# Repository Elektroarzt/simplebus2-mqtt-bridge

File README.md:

# Simplebus2 MQTT Bridge 

### Table of contents
[1. Overview](#Overview)  
[2. Software](#Software)  
[3. Hardware](#Hardware)  
[4. Mechanics](#Mechanics)  
[5. Disclaimer](#Disclaimer)  
[6. Credits](#Credits) 

## Overview

This project focuses on integrating Comelit intercom systems running the Simplebus2 protocol into a Smart Home, typically equipped with an MQTT broker for information exchange. The following functions have been implemented:

-   Doorbell signal main entrance
-   Doorbell signal apartment door
-   Opening main entrance door
-   Ring-to-Open (automatic opening)
-   Permanent web configuration UI (dark theme)
-   Home Assistant MQTT auto-discovery
-   Configurable MQTT topic prefix (default `SimpleBus`)
-   WiFi provisioning portal (first boot / factory reset)
-   Teach-in of intercom address
-   OTA updates (URL or file upload)

**Current firmware: 2.0.0** — see [software/docs/RELEASE-NOTES.md](software/docs/RELEASE-NOTES.md) and the [setup guide](software/docs/SETUP-GUIDE.md).

## Software

### Build and flash (PlatformIO)

```bash
cd software
pio run                 # build
pio run -t upload       # flash via USB
```

Target: ESP32-C3 (`esp32-c3-devkitm-1` / Seeed XIAO ESP32C3).

Pre-built binaries for **v2.0.0**:

| File | Use |
|------|-----|
| [`software/firmware/simplebus2-firmware-2.0.0.bin`](software/firmware/simplebus2-firmware-2.0.0.bin) | OTA / app update (same settings version only — see upgrade note) |
| [`software/firmware/simplebus2-merged-2.0.0.bin`](software/firmware/simplebus2-merged-2.0.0.bin) | Full flash from `0x0` (after erase) |

### First boot — WiFi

On first boot (or after factory reset) the bridge opens AP **`Simplebus2-Bridge`** (open network). Connect and open `http://192.168.4.1/` to set home WiFi. After joining the LAN, open:

- `http://Simplebus2-Bridge.local/` or the device IP

### Permanent web interface

Status, WiFi, MQTT (broker, credentials, **topic prefix**), device parameters (address, gain, threshold, Ring-to-Open duration), OTA, restart / factory reset:

ESP32 WiFi is **2.4 GHz only**. Prefer Chrome or Edge for OTA upload.

### Hardware tuning

**Gain** and **threshold (mV)** adapt to cable length and bus loading. Gain ≈ OPV amplification; threshold = comparator level before the signal reaches the ESP32. **Gain 20 / threshold 600 mV** works well for ~20 m cable in tested installations. See also [software/docs/tuning-process.md](software/docs/tuning-process.md).

### Ring-to-Open

Enable via MQTT (`<prefix>/RingToOpen`) or Home Assistant switch. Duration is set in the web UI or via `<prefix>/SetRingToOpenTime` (1–1440 minutes). **Ring-to-Open only opens on Entry Door rings**, not Floor Door. After a successful auto-open, RtO turns off.

### Firmware update (OTA)

In the web UI: paste an HTTP URL to a `.bin` and **OTA Flash**, or upload `simplebus2-firmware-2.0.0.bin` via **Upload & Flash**. Within the same settings layout version, EEPROM is kept — see **Upgrading from older firmware** below.

### Address adjustment

Each intercom unit has an 8-bit address (DIP switch S1, LSB). Example table:

 Switch No.| 1 | 2 | 3 | 4 |  5 |  6 |  7 |  8  |
 --------- |:-:|:-:|:-:|:-:|:--:|:--:|:--:|:---:|
 Value     | 1 | 2 | 4 | 8 | 16 | 32 | 64 | 128 |

Teach-in: hold SW1 3–4 s (LED double-blink), then ring within 3 minutes — or use MQTT `StartTeachIn` / set address in the web UI.

### MQTT data structure

Default topic prefix: **`SimpleBus`** (configurable). Change in the web UI if you prefer another root.

**Published topics**

 Topic                          | Values         | Notes
 ------------------------------ |:--------------:| ---------------------------------------------------
 `<prefix>/FloorDoor`           | ON             | bell rings on floor door of apartment
 `<prefix>/EntryDoor`           | ON             | bell rings on entry door of building
 `<prefix>/RingToOpenStatus`    | ON / OFF       | Ring-to-Open active or off (retained)
 `<prefix>/RingToOpenOpened`    | ON             | door opened via Ring-to-Open
 `<prefix>/RingToOpenTime`      | minutes        | current RtO duration (retained)
 `<prefix>/Heartbeat`           | ON             | every 5 min
 `<prefix>/availability`        | online         | published on connect

**Subscribed topics**

 Topic                          | Values         | Notes
 ------------------------------ |:--------------:| ---------------------------------------------------
 `<prefix>/OpenDoor`            | ON             | open the door
 `<prefix>/RingToOpen`          | ON / OFF / min | enable RtO (optional duration)
 `<prefix>/SetRingToOpenTime`   | 1 … 1440       | set RtO duration in minutes
 `<prefix>/SetGain`             | 2 … 40         | amplifier gain (default 20)
 `<prefix>/SetComparatorVoltage`| 100 … 1500     | threshold mV (default 600)
 `<prefix>/StartConfigMode`     | ON             | start WiFi AP portal
 `<prefix>/StartTeachIn`        | ON / OFF       | teach-in / cancel
 `<prefix>/Restart`             | ON             | restart ESP32

### Home Assistant

On MQTT connect the bridge publishes MQTT discovery. Entities appear under device **Simplebus2 Bridge** (Entry/Floor doorbell, Open Door button, Ring-to-Open switch & duration, etc.). Details: [software/docs/SETUP-GUIDE.md](software/docs/SETUP-GUIDE.md).

### Highlights vs previous public firmware

- **Robust Simplebus2 bus decoder** — state machine + ISR ring buffer, tighter timing, longer duplicate window (fixes double publish / false positives); see [RELEASE-NOTES](software/docs/RELEASE-NOTES.md)
- Permanent web UI, configurable MQTT prefix (**default still `SimpleBus`**), HA MQTT discovery, safer ESP32-C3 restart (`safeRestart` / GPIO9)

### Upgrading from older firmware (previous public sketch)

**Device settings in EEPROM are not migrated.** The old firmware stored MQTT/broker/gain/address without a settings-version header; this release uses a new `Settings` layout (`SETTINGS_VERSION = 3`). On first boot after the upgrade the bridge detects a version mismatch, **wipes those EEPROM fields, and loads factory defaults**.

| Data | Survives upgrade? |
|------|-------------------|
| WiFi SSID / password (WiFiManager NVS) | Usually **yes** |
| MQTT broker, user, password | **No — re-enter** |
| Topic prefix | **No — defaults to `SimpleBus`** |
| Intercom address, gain, threshold | **No — re-enter** |
| Ring-to-Open duration / automation flag | **No — re-enter** |

After flashing, open the web UI (`http://Simplebus2-Bridge.local/` or the device IP) and re-enter MQTT + device parameters. Have your previous values ready before you update.

### Breaking changes (previous public firmware → 2.0.0)

- **EEPROM layout incompatible** — MQTT and device settings must be re-entered (see above)
- WiFi AP name **`Config_MQTT_SimpleBus_2` / `Config_MQTT_SimpleBus2` → `Simplebus2-Bridge`**
- Configuration primarily via **permanent web UI** (not only WiFiManager menus)

### Dependencies (PlatformIO)

| Component | Version | Notes |
| --------- | ------- | ----- |
| PubSubClient | ^2.8 | `lib_deps` |
| WiFiManager | ^2.0.17 | `lib_deps` |
| Debounce | local | `software/lib/Debounce` |
| EEPROM, WiFi, Wire, WebServer, HTTPUpdate | Arduino-ESP32 | framework |

### Issue fixes in 2.0.0

- Correct comparison in `writeMessageToIntercom` (`msgCode == MSG_OPEN_DOOR`) — fixes [#13](https://github.com/Elektroarzt/simplebus2-mqtt-bridge/issues/13)
- `structInitialized()` uses `strlen` / settings version instead of `sizeof` on char arrays — [#13](https://github.com/Elektroarzt/simplebus2-mqtt-bridge/issues/13)
- HA discovery / availability and RingToOpenTime sync — see release notes

## Hardware

The electronics draw power from the bus voltage and require no additional power source. A Seeed Studio XIAO ESP32C3 serves as the controller board.

### Expansion pin header J2
For future use this pin header can connect to a piggy-back. The M2.5 hole in the neighborhood can be used to secure a sandwich PCBA.

 Signal Name   | Pin  | Notes
 ------------- |:----:| --------------------------------------------------------------------------------------
 D6            | 1    | GPIO 21 of ESP32 (D6 of XIAO module pinout)
 3V3           | 2    | directly connected to 3.3V plane
 D3            | 3    | GPIO 5 of ESP32 (D3 of XIAO module pinout, outputs PWM signal at boot, strapping pin)
 GND           | 4    | directly connected to GND plane
 
### Debug pin header J3
Meant for debugging, header can be populated optionally. The following signals can be measured against GND:

 Signal Name   | Pin  | Notes
 ------------- |:----:| ----------------------------------------------------------------------------
 D1            | 1    | voltage divider 1, reference voltage of OPV filter stage 1 ('gain' parameter)
 S2            | 2    | cleaned payload signal of Simplebus2
 D2            | 3    | voltage divider 2, reference voltage of comparator ('level' parameter)
 GND           | 4    | directly connected to GND plane

### Filter
In the schematics two filters can be found, one low pass (C5 and R5) and one high pass sallen key active filter with a gain of 2. Between those two filters there is signal amplifier which can be set individually to compensate for a long bus wire. The goal is to filter and amplify the incoming 25 kHz signal.

R1 and R11 are alternative positions to select signal conditioning by hardware (comparator U6) or direct input of the signal into the ESP32. In the second case the firmware should do the signal conditioning via DSP routines or similar. At the moment the DSP option is not implemented in the firmware and is meant for future use, so option "OPV" is default. To change this, desolder R11 and close R1 with a solder drop or a 0Ohms resistor.

## Printed Circuit Board (PCB)

The PCB was designed with KiCAD using through-hole technology (THT) and surface-mount device technology (SMD) to match the limited space requirements. Top layer is 3,3V plane and bottom is GND plane.
If someone is interested in a complete bridge including all parts (PCBA, ESP32, housing, etc.) you can contact me under elektroarzt@digital-filestore.de.

## Mechanics

The entire electronics assembly fits into a flush-mounted switch box, resulting in a streamlined enclosure. The latch was designed as a snap closure, eliminating the need for additional mechanical components beyond the housing shells.

A second option for the housing is a DIN rail enclosure. For this, I have created an alternative bottom shell with a builtin clip that can be directly clicked onto a DIN rail. It should not be printed in PLA, use a somewhat flexible filament like PETG. Otherwise, there is a risk of cracking the clip if released from the DIN rail again. The top part of the housing is identical to the flush-mounted version.

### Antenna
The antenna is mounted inside the housing with adhesive tape. A small cable channel exists for the antenna cable within the housing. Be careful while inserting the PCB in the housing not to shear off the antenna cable if it is not inserted properly into the cable channel.

### USB connector
The USB-C socket is externally routed, allowing for easy firmware updates.

### LED and button
The onboard LED features a simple light guide, making it visible externally when the housing is closed. The onboard button is operated with a small axis embedded in the housing.

### Housing
The housing was designed in Autodesk Fusion 360 and 3D-printed in three colors on Bambu Lab P1S printer:
-   LED diffuser: transparent filament
-   Housing: black filament
-   Labeling: white filament

For the type of filament every material is suitable that has low stringing tendency. PETG works for me without needing supports. 0.2mm layer height does a good job on a 0.4mm standard nozzle.

## Disclaimer
> :warning: **WARNING**: You may only **USE THIS PROJECT AT YOUR OWN RISK**. The
  information provided is meant to be helpful but may contain errors or may be
  misinterpreted. Neither myself nor any of the contributors to this project
  provide any warranty or will assume any responsibility for any damage you
  cause yourself or others by using this project.

## Credits
The project originated from the excellent foundational work on the Simplebus2 protocol by [plusvic](https://github.com/plusvic). These fundamentals will not be reiterated and can be found [here](https://github.com/plusvic/simplebus2-intercom).

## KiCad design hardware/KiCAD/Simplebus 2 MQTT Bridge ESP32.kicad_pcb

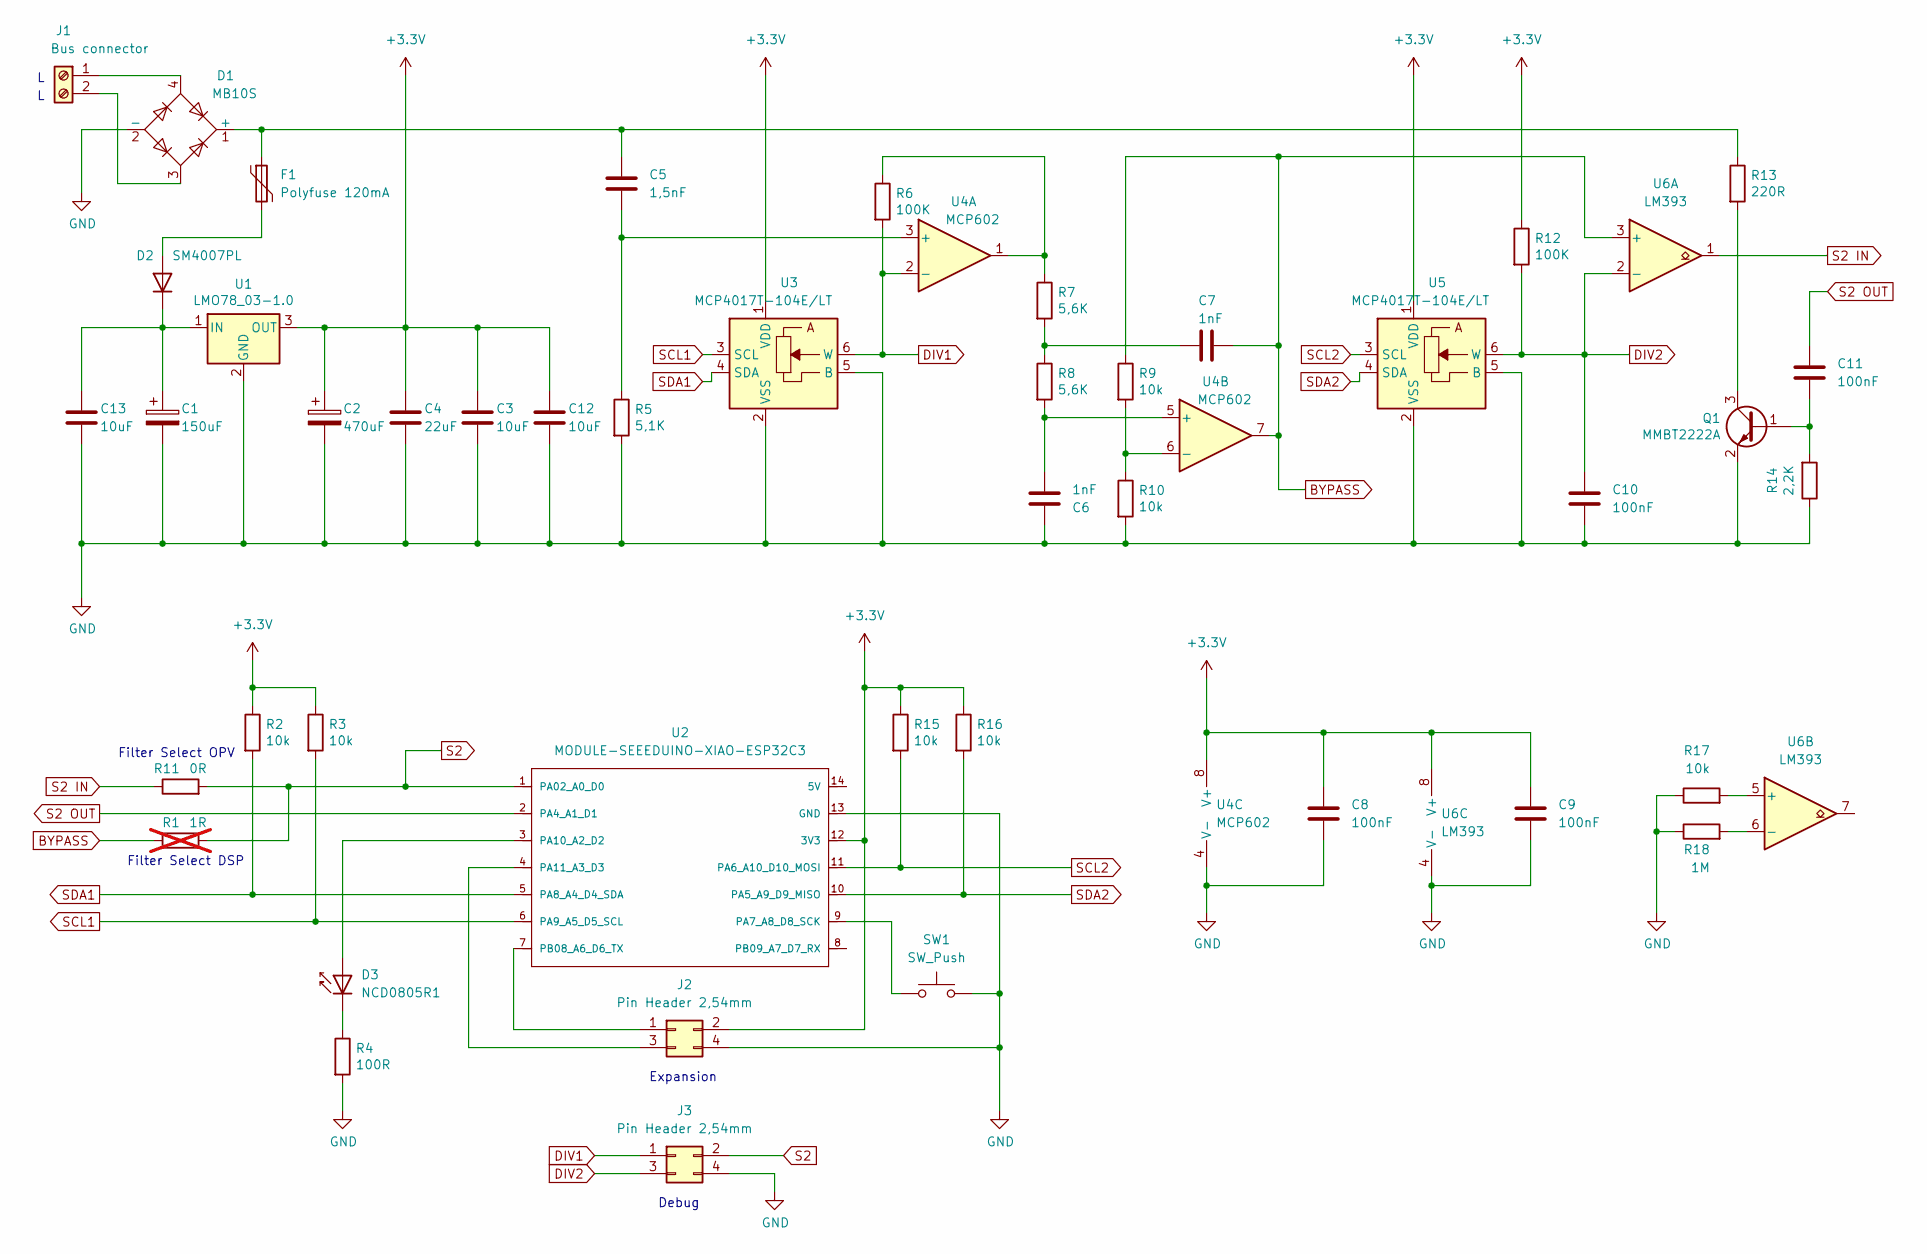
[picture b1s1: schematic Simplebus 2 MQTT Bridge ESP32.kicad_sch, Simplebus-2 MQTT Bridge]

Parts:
C1: 150uF; C_Elec_8x10.2; LCSC C87860
C2: 470uF; CP_Elec_6.3x7.7; LCSC C445248
C3, C12, C13: 10uF; C_1206_3216Metric_Pad1.33x1.80mm_HandSolder; LCSC C513774
C4: 22uF; C_1206_3216Metric_Pad1.33x1.80mm_HandSolder; LCSC C5672
C5: 1,5nF; C_0805_2012Metric_Pad1.18x1.45mm_HandSolder; LCSC C1717
C6, C7: 1nF; C_0805_2012Metric_Pad1.18x1.45mm_HandSolder; LCSC C46653
C8, C9, C10: 100nF; C_0805_2012Metric_Pad1.18x1.45mm_HandSolder; LCSC C28233
C11: 100nF; C_0805_2012Metric_Pad1.18x1.45mm_HandSolder; LCSC C49678
D1: MB10S; SOIC245P670X290-4N; LCSC C2488
D2: SM4007PL; D_SOD-123F; LCSC C64898
D3: NCD0805R1; LED_0805_2012Metric_Pad1.15x1.40mm_HandSolder; LCSC C84256
F1: Polyfuse 120mA; C_1206_3216Metric_Pad1.33x1.80mm_HandSolder; LCSC C20982
J1: Bus connector; PinHeader_1x02_P5.75mm_Vertical
J2, J3: Pin Header 2,54mm; PinHeader_2x02_P2.54mm_Vertical
Q1: MMBT2222A; SOT-23; LCSC C8512
R1: 1R; R_0805_2012Metric_Pad1.20x1.40mm_HandSolder; LCSC C25271; not fitted
R2, R3, R9, R10, R15, R16, R17: 10k; R_0805_2012Metric_Pad1.20x1.40mm_HandSolder; LCSC C17414
R4: 100R; R_0805_2012Metric_Pad1.20x1.40mm_HandSolder; LCSC C17408
R5: 5,1K; R_0805_2012Metric_Pad1.20x1.40mm_HandSolder; LCSC C27834
R6, R12: 100K; R_0805_2012Metric_Pad1.20x1.40mm_HandSolder; LCSC C149504
R7, R8: 5,6K; R_0805_2012Metric_Pad1.20x1.40mm_HandSolder; LCSC C4382
R11: 0R; R_0805_2012Metric_Pad1.20x1.40mm_HandSolder; LCSC C17477
R13: 220R; R_0805_2012Metric_Pad1.20x1.40mm_HandSolder; LCSC C17557
R14: 2,2K; R_0805_2012Metric_Pad1.20x1.40mm_HandSolder; LCSC C17520
R18: 1M; R_0805_2012Metric_Pad1.20x1.40mm_HandSolder; LCSC C17514
SW1: SW_Push; SW_Push_1P1T_XKB_TS-1187A; LCSC C318884
U1: LMO78_03-1.0; SIP-3 GAPTEC LMO78_xx-x.x
U2: MODULE-SEEEDUINO-XIAO-ESP32C3; MODULE14P-THT-2.54-21X17.8MM
U3, U5: MCP4017T-104E/LT; SOT-363_SC-70-6; LCSC C510890
U4: MCP602; SOIC-8_3.9x4.9mm_P1.27mm; LCSC C29605
U6: LM393; SOIC-8_3.9x4.9mm_P1.27mm; LCSC C7955

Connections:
+3.3V: C2.1, C3.1, C4.1, C8.1, C9.1, C12.1, J2.2, R2.1, R3.1, R12.1, R15.1, R16.1, U1.3 (OUT), U2.12 (3V3), U3.1 (VDD), U4.8 (V+), U5.1 (VDD), U6.8 (V+)
BYPASS: C7.1, R1.1, R9.1, U4.7, U6.3 (+)
DIV1: J3.1, R6.2, U3.6 (W), U4.2 (-)
DIV2: C10.1, J3.3, R12.2, U5.6 (W), U6.2 (-)
GND: C1.2, C2.2, C3.2, C4.2, C6.2, C8.2, C9.2, C10.2, C12.2, C13.2, D1.2 (-), J2.4, J3.4, Q1.2 (E), R4.2, R5.2, R10.2, R14.1, R17.1, R18.1, SW1.2, U1.2 (GND), U2.13 (GND), U3.2 (VSS), U3.5 (B), U4.4 (V-), U5.2 (VSS), U5.5 (B), U6.4 (V-)
unnamed: C7.2, R7.2, R8.1
unnamed: C5.1, D1.1 (+), F1.1, R13.1
unnamed: D2.2 (A), F1.2
unnamed: C1.1, C13.1, D2.1 (K), U1.1 (IN)
unnamed: D3.2 (A), U2.3 (PA10_A2_D2)
unnamed: D3.1 (K), R4.1
unnamed: D1.4, J1.1
unnamed: D1.3, J1.2
unnamed: J2.1, U2.7 (PB08_A6_D6_TX)
unnamed: J2.3, U2.4 (PA11_A3_D3)
unnamed: C11.2, Q1.1 (B), R14.2
unnamed: Q1.3 (C), R13.2
unnamed: R6.1, R7.1, U4.1
unnamed: SW1.1, U2.9 (PA7_A8_D8_SCK)
unnamed: C5.2, R5.1, U4.3 (+)
unnamed: C6.1, R8.2, U4.5 (+)
unnamed: R9.2, R10.1, U4.6 (-)
unnamed: R17.2, U6.5 (+)
unnamed: R18.2, U6.6 (-)
S2: J3.2, R1.2, R11.2, U2.1 (PA02_A0_D0)
S2 IN: R11.1, U6.1
S2 OUT: C11.1, U2.2 (PA4_A1_D1)
SCL1: R3.2, U2.6 (PA9_A5_D5_SCL), U3.3 (SCL)
SCL2: R15.2, U2.11 (PA6_A10_D10_MOSI), U5.3 (SCL)
SDA1: R2.2, U2.5 (PA8_A4_D4_SDA), U3.4 (SDA)
SDA2: R16.2, U2.10 (PA5_A9_D9_MISO), U5.4 (SDA)

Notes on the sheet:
Debug
Filter Select DSP
Expansion
Filter Select OPV

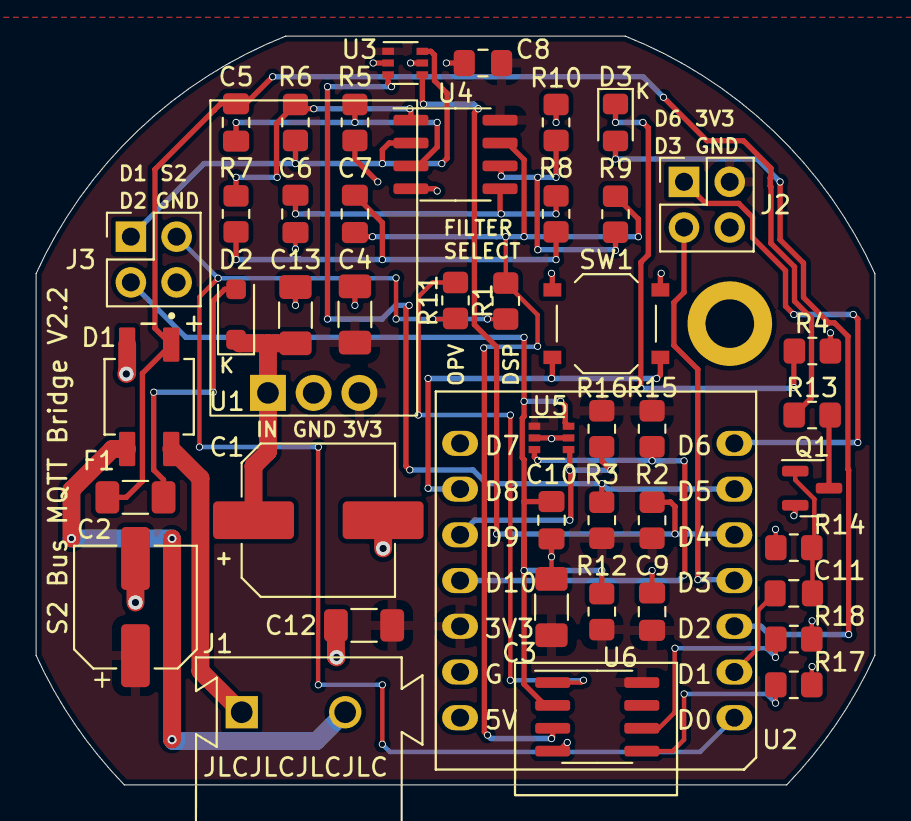
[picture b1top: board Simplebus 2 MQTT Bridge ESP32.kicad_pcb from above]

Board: 2 copper layers, 46.6 x 41.6 mm, 46 parts (0 on the bottom side), 31 nets.

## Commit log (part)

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2024-01-11 README.md aktualisieren
2024-01-11 Added mechanics
2024-01-13 Rename Schematics V2.1.pdf
2024-01-20 First release candidate
    Thanks to Plusvic for the initial great work and decoding the bus.
2024-01-21 Schematic and PCB V2.2
2024-01-28 ibom V2.2
2024-02-06 Parameter update for HW V2.2
2024-02-08 Added KiCAD project
2024-02-13 I2C bugfix, bugfix SetRingToOpenTime, added teach in for intercom address
    Added teach in for intercom address with long press 2-3 seconds.
    Short press opens wifimanager
2024-02-14 Added intercom adress to onfiguration
2024-02-17 Update Bambu Lab project
2024-03-01 Added libs and bugfixes
    +Works now on doors without a screen
    +Bugfix I2C resistor
2024-03-13 Update main.cpp
    Bugfix i2c
2024-03-16 Set compVoltage and Gain with MQTT
    Set CompVoltage and Gain with MQTT
2024-03-16 Update README.md
    Added MQTT commands for gain and threshold
2024-03-18 Bugfix and tighter timings
    +Tighter Timings
    +Better noise reduction and filtering for longer high signals
    +Added teach in and wificonfig MQTT Command
2024-03-18 Added MQTT command
    +Mqtt comand if the door is opened
2024-03-18 Update README.md
    Added new MQTT commands for teach-in and web configuration
2024-03-18 Update README.md
    Added MQTT topic for ring to open status
2024-03-23 Update README.md
    Linked to ESPhome project of se-bastiaan
2024-03-23 Update README.md
    Restructured Overview
2024-03-23 Update README.md
    Updated pictures to new version of housing
2024-04-01 Now detecting floordoor and new features
    +Floordor detection
    +Restart command
    +Hearbeat every 5 minutes
2024-04-01 Update README.md
    MQTT Update
    + Heartbeat
    + Feedback if 'ring-to-open' opened the door
    + Reset ESP32
    Improved ring recognition
2024-04-01 Bugfix added missing MQTT commands
    Bugfix added missing MQTT commands
2024-04-01 Minor bugfix
    +Heartbeat now sends directyl after Reboot one time
2024-04-02 Bugfix teach in and configmode
2024-04-02 Changed default values
2024-04-02 New pictures after redesign of housing
2024-04-02 Remove SW filter, update standard gain / threshold
    - Removed software filter, was experimental and had no positive function
    - updated gain and threshold standard values to 20 / 600
2024-04-02 Update README.md
    - Removed software filter, was experimental and had no positive function
    - updated gain and threshold standard values to 20 / 600
2024-05-02 Added bin file
2024-05-09 Added stability badge
2025-03-11 Added Housing for DIN Rail Mount
